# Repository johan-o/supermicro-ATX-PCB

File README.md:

# supermicro-ATX-PCB
This project is for a PCB that adapts a Supermicro case to take normal ATX motherboards, equivalent in function to the CBL-0084L.
However, the PCB is cheaper to get in large quantities (~$34 for 20 PCBs vs $7 for each cable).

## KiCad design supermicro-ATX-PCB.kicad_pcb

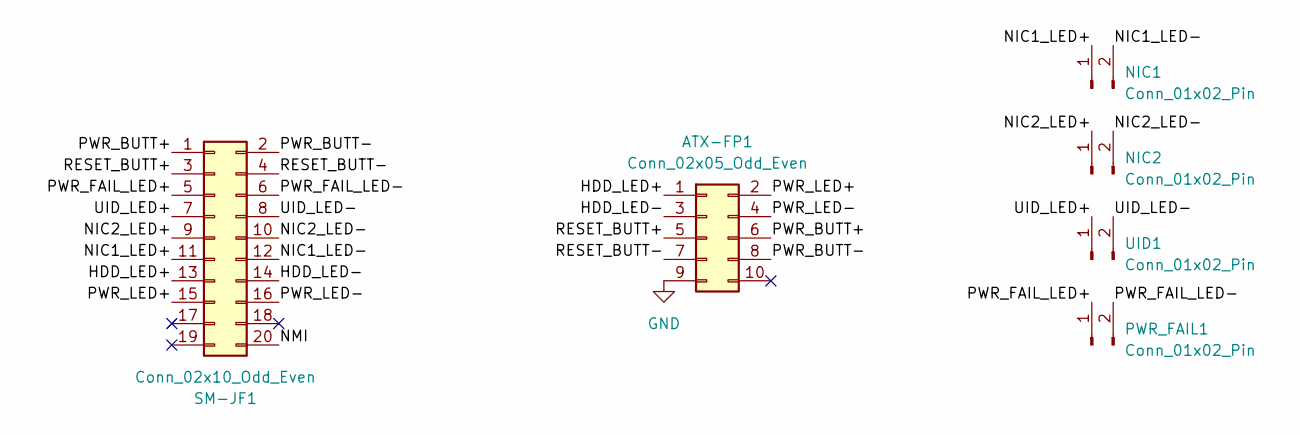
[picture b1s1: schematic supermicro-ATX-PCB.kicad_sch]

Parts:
ATX-FP1: Conn_02x05_Odd_Even; PinSocket_2x05_P2.54mm_Vertical
NIC1, NIC2: Conn_01x02_Pin; PinHeader_2x01_P2.54mm_Vertical
PWR_FAIL1: Conn_01x02_Pin; PinHeader_2x01_P2.54mm_Vertical
SM-JF1: Conn_02x10_Odd_Even; PinHeader_2x10_P2.54mm_Vertical
UID1: Conn_01x02_Pin; PinHeader_2x01_P2.54mm_Vertical

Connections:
/HDD_LED+: ATX-FP1.1, SM-JF1.13
/HDD_LED-: ATX-FP1.3, SM-JF1.14
/NIC1_LED+: NIC1.1, SM-JF1.11
/NIC1_LED-: NIC1.2, SM-JF1.12
/NIC2_LED+: NIC2.1, SM-JF1.9
/NIC2_LED-: NIC2.2, SM-JF1.10
/NMI: SM-JF1.20
/PWR_BUTT+: ATX-FP1.6, SM-JF1.1
/PWR_BUTT-: ATX-FP1.8, SM-JF1.2
/PWR_FAIL_LED+: PWR_FAIL1.1, SM-JF1.5
/PWR_FAIL_LED-: PWR_FAIL1.2, SM-JF1.6
/PWR_LED+: ATX-FP1.2, SM-JF1.15
/PWR_LED-: ATX-FP1.4, SM-JF1.16
/RESET_BUTT+: ATX-FP1.5, SM-JF1.3
/RESET_BUTT-: ATX-FP1.7, SM-JF1.4
/UID_LED+: SM-JF1.7, UID1.1
/UID_LED-: SM-JF1.8, UID1.2
GND: ATX-FP1.9

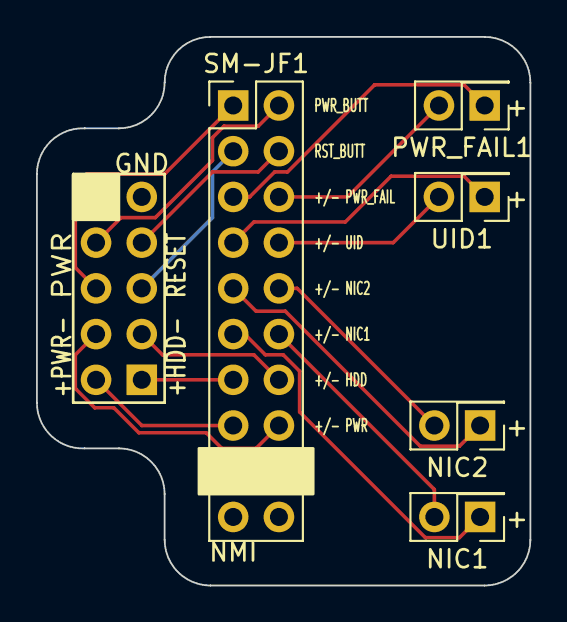
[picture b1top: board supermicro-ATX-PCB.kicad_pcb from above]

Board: 2 copper layers, 27.4 x 30.5 mm, 6 parts (1 on the bottom side), 16 nets.

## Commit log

2023-11-26 added finished THT PCB
2023-11-26 added through hole for female header
2023-11-26 testing SMD Female
2023-11-26 added routing for SMT ATX Female
2023-11-26 added THT board
2023-11-26 added README
2023-12-29 switched polarity of LEDs, isolated all terminals of buttons
